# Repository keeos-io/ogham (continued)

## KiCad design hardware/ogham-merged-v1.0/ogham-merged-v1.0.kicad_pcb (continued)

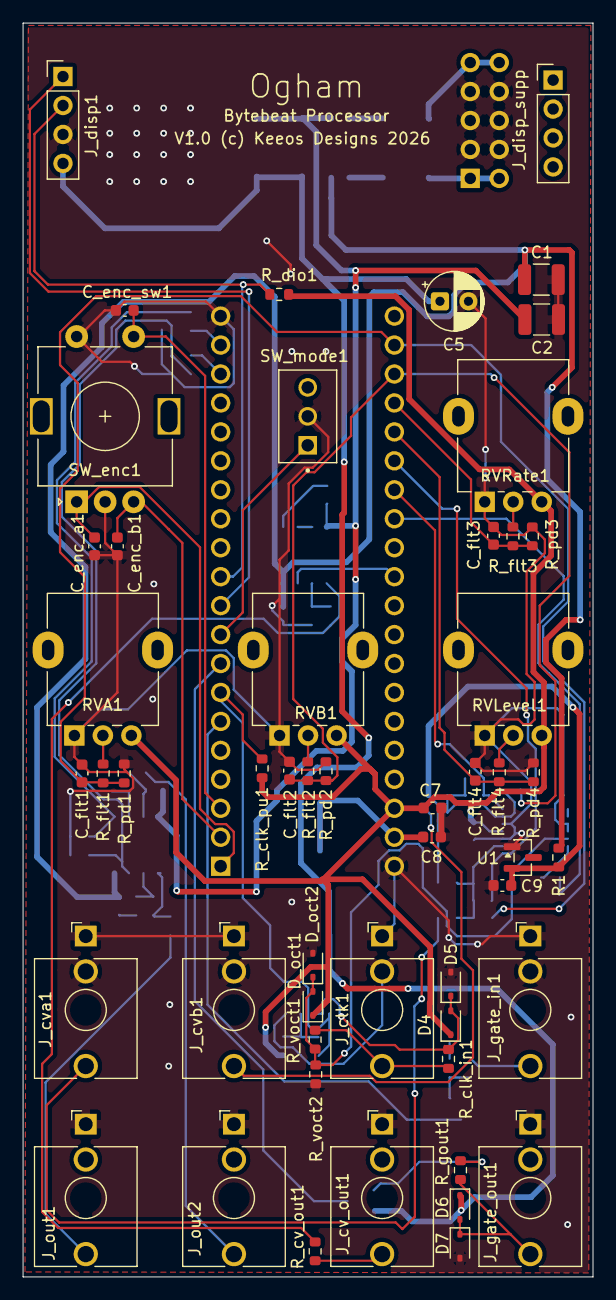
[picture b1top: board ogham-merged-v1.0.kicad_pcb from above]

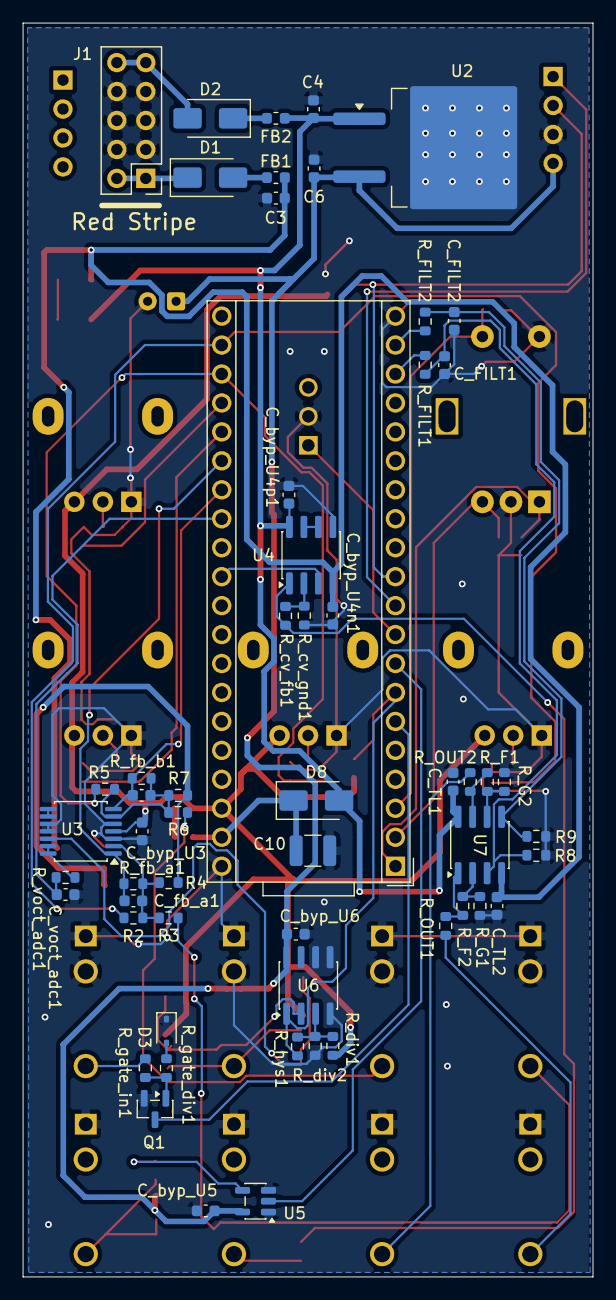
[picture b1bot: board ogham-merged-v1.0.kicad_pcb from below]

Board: 2 copper layers, 50.0 x 110.0 mm, 109 parts (57 on the bottom side), 61 nets.

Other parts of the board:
J_disp_supp: PinHeader_1x04_P2.54mm_Vertical

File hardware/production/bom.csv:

Designator,Footprint,Quantity,Value,LCSC Part #
A1,Electrosmith_Daisy_Seed,1,Electrosmith_Daisy_Seed_Rev4,
"C1, C10, C2",1210,3,10uF,C138687
"C3, C4, C6, C7, C8, C9, C_BYP_U3, C_BYP_U4N1, C_BYP_U4P1, C_BYP_U5, C_BYP_U6, C_ENC_A1, C_ENC_B1, C_ENC_SW1, C_FLT1, C_FLT2, C_FLT3, C_FLT4, C_TL1, C_TL2",0603,20,100nF,C14663
C5,CP_Radial_D5.0mm_P2.50mm,1,10uF,TAP106J016SCS
"C_FB_A1, C_FB_B1, C_VOCT_ADC1",0603,3,1nF,C1588
"C_FILT1, C_FILT2",0603,2,2.2nF,C1604
"D1, D2, D8",D_SMA,3,SS14,C2480
D3,D_SOD-323,1,1N4148,C2128
"D4, D5, D_OCT1, D_OCT2",D_SOD-323,4,BAT54WS,C22629
"D6, D7",D_SOD-323,2,1N5819WS,C191023
"FB1, FB2",0603,2,BLM18PG121,C14709
J1,PinHeader_2x05_P2.54mm_Vertical,1,Eurorack_Power,
"J_CLK1, J_CVA1, J_CVB1, J_GATE_IN1",Jack_3.5mm_QingPu_WQP-PJ398SM_Vertical_CircularHoles,4,AudioJack2_SwitchT,
J_CV_OUT1,Jack_3.5mm_QingPu_WQP-PJ398SM_Vertical_CircularHoles,1,CV_OUT,
J_DISP1,PinHeader_1x04_P2.54mm_Vertical,1,TM1637,
J_DISP_SUPP,PinHeader_1x04_P2.54mm_Vertical,1,PinHeader_1x04_P2.54mm_Vertical,
J_GATE_OUT1,Jack_3.5mm_QingPu_WQP-PJ398SM_Vertical_CircularHoles,1,GATE_OUT,
J_OUT1,Jack_3.5mm_QingPu_WQP-PJ398SM_Vertical_CircularHoles,1,OUT1,
J_OUT2,Jack_3.5mm_QingPu_WQP-PJ398SM_Vertical_CircularHoles,1,OUT2,
Q1,SOT-23,1,MMBT3904,C20526
"R1, R_CLK_IN1, R_CLK_PU1, R_CV_GND1, R_DIO1, R_DIV1, R_DIV2, R_F1, R_F2, R_VOCT1",0603,10,10k,C25804
"R2, R5, R8, R9, R_FB_A1, R_FB_B1, R_GATE_IN1, R_HYS1, R_PD1, R_PD2, R_PD3, R_PD4",0603,12,100k,C25803
"R3, R6",0603,2,470k,C23178
"R4, R7",0603,2,200k,C25811
"RVA1, RVB1, RVLEVEL1, RVRATE1",Potentiometer_Alpha_RD901F-40-00D_Single_Vertical,4,10k,
R_CV_FB1,0603,1,20k,C4184
"R_CV_OUT1, R_FLT1, R_FLT2, R_FLT3, R_FLT4, R_GOUT1, R_OUT1, R_OUT2, R_VOCT_ADC1",0603,9,1k,C21190
"R_FILT1, R_FILT2",0603,2,470,C23179
"R_G1, R_G2",0603,2,2.7k,C13167
R_GATE_DIV1,0603,1,33k,C4216
R_VOCT2,0603,1,18k,C25810
SW_ENC1,RotaryEncoder_Alps_EC11E-Switch_Vertical_H20mm,1,Encoder,
SW_MODE1,SW_2MS1T1B1M2QES,1,SW_SPDT,
U1,SOT-23,1,LM4040-5.0,C156302
U2,TO-263-2,1,L7805,C15077
U3,TSSOP-14_4.4x5mm_P0.65mm,1,MCP6004,C50282
"U4, U7",SOIC-8_3.9x4.9mm_P1.27mm,2,TL072,C67473
U5,SOT-23-5,1,74AHCT1G125,C7484
U6,SOIC-8_3.9x4.9mm_P1.27mm,1,LM393,C136033

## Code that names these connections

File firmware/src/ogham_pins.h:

// -----------------------------------------------------------------------------
// Ogham — a dual-voice bytebeat synthesizer for Eurorack
//
// Author:     Steven Collins, 2026, Keeos.io
// Copyright:  (c) 2026 Steven Collins
//
// SPDX-FileCopyrightText: 2026 Steven Collins <https://keeos.io>
// SPDX-License-Identifier: MIT
//
// This file is part of the Ogham firmware. See LICENSE-firmware.txt at the
// repository root for the full licence text.
// https://github.com/stevec64/keeos-ogham
// -----------------------------------------------------------------------------

#pragma once
// Ogham Eurorack Module — Pin Assignments
// Source of truth: KiCad schematic v0.4 (ERC clean)
// See hardware/ogham/ERC_manual_review.md for full pin table

namespace ogham {

// --- Encoder (directly connected, active-low with pull-ups) ---
constexpr int ENC_A  = 0;   // GPIO0, Seed pin 1
constexpr int ENC_B  = 1;   // GPIO1, Seed pin 2
constexpr int ENC_SW = 2;   // GPIO2, Seed pin 3

// --- Gate / Clock (active-high after transistor/comparator inversion) ---
constexpr int GATE_IN  = 5;  // GPIO5, Seed pin 6  — via MMBT3904 NPN
constexpr int CLK_IN   = 6;  // GPIO6, Seed pin 7  — via LM393 comparator
constexpr int GATE_OUT = 7;  // GPIO7, Seed pin 8  — via 74AHCT1G125 buffer

// --- TM1637 Display ---
constexpr int TM1637_CLK = 9;   // GPIO9,  Seed pin 10
constexpr int TM1637_DIO = 10;  // GPIO10, Seed pin 11 — open-drain, 10k pull-up

// --- ADC Channels (D15-D21 = ADC0-ADC6) ---
constexpr int POT_A     = 15;  // ADC0, Seed pin 22
constexpr int POT_B     = 16;  // ADC1, Seed pin 23
constexpr int POT_RATE  = 17;  // ADC2, Seed pin 24
constexpr int POT_LEVEL = 18;  // ADC3, Seed pin 25
constexpr int CV_A      = 19;  // ADC4, Seed pin 26 — via MCP6004 (inverted)
constexpr int CV_B      = 20;  // ADC5, Seed pin 27 — via MCP6004 (inverted)
constexpr int VOCT_ADC  = 21;  // ADC6, Seed pin 28 (A6/D21) — V/oct tap on the Clock jack
constexpr int NUM_ADC_CHANNELS = 7;

// --- Mode toggle: Clock (tempo) <-> V/oct (pitch) ---
// Dailywell SPDT: common (pin 2) -> GND, throw (pin 1) -> this GPIO w/ pull-up.
constexpr int MODE_SW   = 8;   // GPIO8, Seed pin 9 (D8 / PG11)

// --- DAC Output ---
constexpr int CV_OUT_DAC = 23;  // DAC_OUT1 / PA4, Seed pin 30

}  // namespace ogham
